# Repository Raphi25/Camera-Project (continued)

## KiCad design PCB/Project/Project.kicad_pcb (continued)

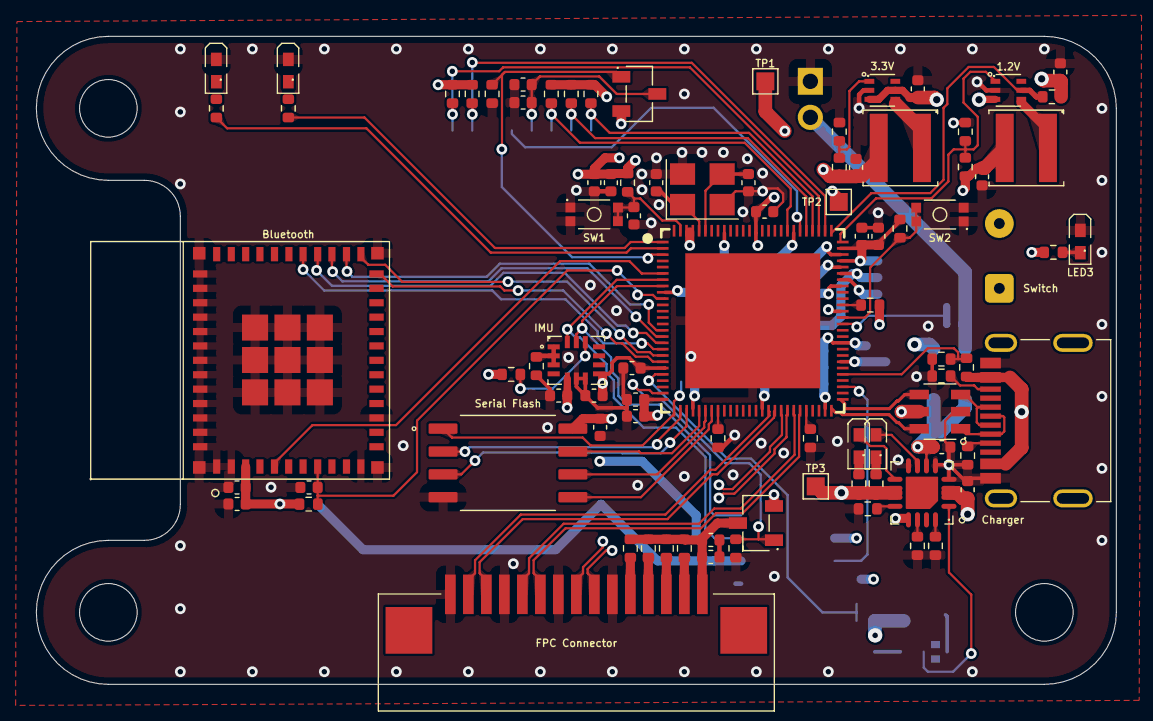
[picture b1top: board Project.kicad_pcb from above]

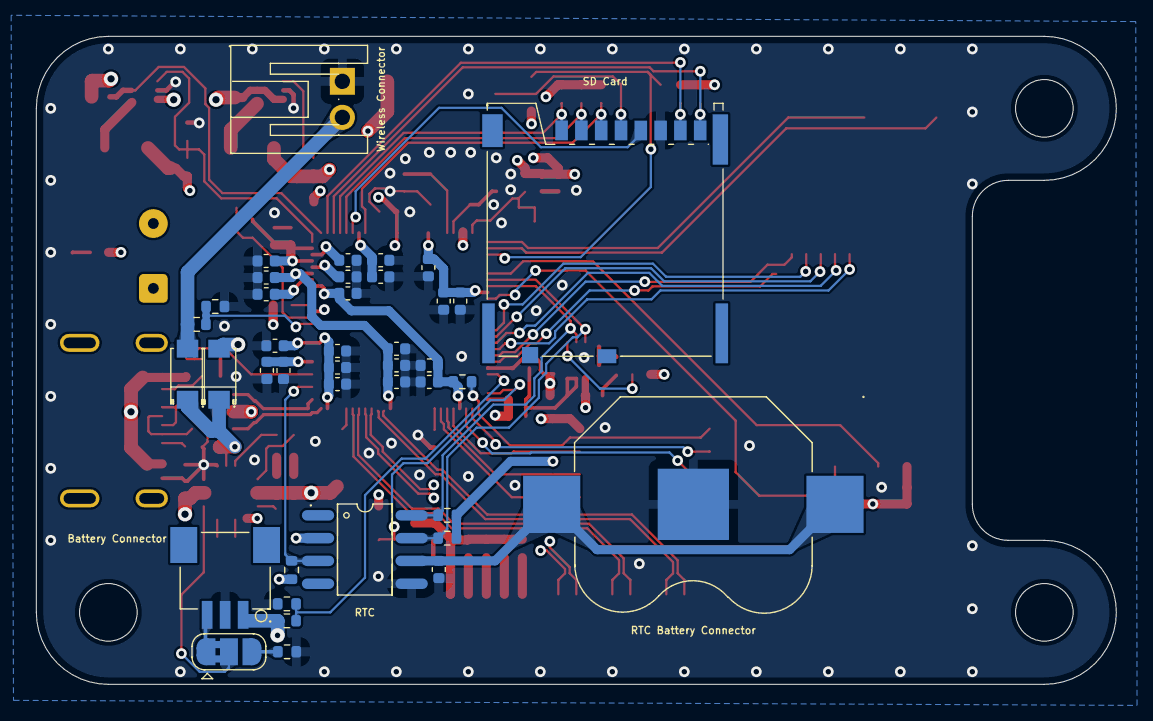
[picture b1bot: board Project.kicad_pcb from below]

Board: 4 copper layers, 60.0 x 36.0 mm, 132 parts (40 on the bottom side), 89 nets.

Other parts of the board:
1.2V, 3.3V: TLV62569PDRLR; SOT-563_L1.6-W1.2-P0.50-LS1.6-BL
Battery Connector: SM03B-SRSS-TB; CONN-SMD_SM03B-SRSS-TB-LF-SN-P
Bluetooth: ESP32-C6-MINI-1-N4; WIFIM-SMD_61P-L16.6-W13.2-P0.80-ESP32-C6-MINI-1-N4
Charger: BQ24074RGTR; QFN-16_L3.0-W3.0-P0.50-TL-EP1.7
FPC Connector: 1.0-15P下接; FPC-SMD_C66660
IMU: LSM6DSOTR; LGA-14_L3.0-W2.5-P0.50-TL
RTC: DS3231MZ+_C722467; SOIC-8_L4.9-W3.9-P1.27-LS6.0-BL
RTC Battery Connector: 3000; BAT-SMD_CR1202
SD Card: 503398-1892; TF-SMD_503398-1892
Serial Flash: W25Q128JVSIQ; SOIC127P790X216-8N
Switch: Conn_01x02; SolderWire-0.1sqmm_1x02_P3.6mm_D0.4mm_OD1mm
Wireless Connector: S2B-PH-K-S; CONN-TH_S2B-PH-K-S-LF-SN

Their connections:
+5V_CH: Charger.6 (EN1), Charger.13 (IN), RTC.2 (VCC); also elsewhere on the board
+5V_WIR: Wireless Connector.2; also elsewhere on the board
+BATT: Battery Connector.1, Charger.2 (BAT), Charger.3 (BAT); also elsewhere on the board
+BATT2: RTC.6 (VBAT), RTC Battery Connector.1 (+), RTC Battery Connector.2 (+); also elsewhere on the board
C6_EN: Bluetooth.8 (EN); also elsewhere on the board
C6_WAKEUP: Bluetooth.5 (IO2); also elsewhere on the board
CSI_CLK_N: FPC Connector.9; also elsewhere on the board
CSI_CLK_P: FPC Connector.8; also elsewhere on the board
CSI_D0_N: FPC Connector.2; also elsewhere on the board
CSI_D0_P: FPC Connector.3; also elsewhere on the board
CSI_D1_N: FPC Connector.5; also elsewhere on the board
CSI_D1_P: FPC Connector.6; also elsewhere on the board
EN_1.2V: 1.2V.5 (EN); also elsewhere on the board
ESP_3V3: Bluetooth.3 (3V3), IMU.5 (VDDIO), IMU.8 (VDD); also elsewhere on the board
ESP_LDO_VO1: Serial Flash.8 (VCC); also elsewhere on the board
ESP_SCL: IMU.13 (SCL), RTC.8 (SCL); also elsewhere on the board
ESP_SDA: IMU.14 (SDA), RTC.7 (SDA); also elsewhere on the board
FB_DCDC: 1.2V.1 (FB); also elsewhere on the board
FLASH_CK: Serial Flash.6 (CLK); also elsewhere on the board
FLASH_CS: Serial Flash.1 (/CS); also elsewhere on the board
FLASH_D: Serial Flash.5 (DI(IO0)); also elsewhere on the board
FLASH_HOLD: Serial Flash.7 (/HOLD/RESET(IO3)); also elsewhere on the board
FLASH_Q: Serial Flash.2 (DO(IO1)); also elsewhere on the board
FLASH_WP: Serial Flash.3 (/WP(IO2)); also elsewhere on the board
GND: 1.2V.2 (GND), 3.3V.2 (GND), Battery Connector.2, Bluetooth.1 (GND), Bluetooth.2 (GND), Bluetooth.11 (GND), Bluetooth.14 (GND), Bluetooth.36 (GND), Bluetooth.37 (GND), Bluetooth.38 (GND), Bluetooth.39 (GND), Bluetooth.40 (GND), Bluetooth.41 (GND), Bluetooth.42 (GND), Bluetooth.43 (GND), Bluetooth.44 (GND), Bluetooth.45 (GND), Bluetooth.46 (GND), Bluetooth.47 (GND), Bluetooth.48 (GND), Bluetooth.49 (GND), Bluetooth.50 (GND), Bluetooth.51 (GND), Bluetooth.52 (GND), Bluetooth.53 (GND), Charger.4 (~CE), Charger.5 (EN2), Charger.8 (VSS), FPC Connector.1, FPC Connector.4, FPC Connector.7, FPC Connector.10, IMU.6 (GND), IMU.7 (GND), RTC.5 (GND), RTC Battery Connector.3 (-), SD Card.6 (VSS), Serial Flash.4 (GND), Wireless Connector.1; also elsewhere on the board
unnamed 37: FPC Connector.11; also elsewhere on the board
unnamed 38: FPC Connector.12; also elsewhere on the board
unnamed 39: FPC Connector.13; also elsewhere on the board
unnamed 40: FPC Connector.14; also elsewhere on the board
unnamed 41: Charger.10 (OUT), Charger.11 (OUT), Switch.1; also elsewhere on the board
unnamed 42: Battery Connector.3; also elsewhere on the board
unnamed 45: Charger.9 (~CHG); also elsewhere on the board
unnamed 47: Charger.7 (~PGOOD); also elsewhere on the board
unnamed 51: FPC Connector.15; also elsewhere on the board
unnamed 52: SD Card.4 (VDD); also elsewhere on the board
unnamed 58: 3.3V.1 (FB); also elsewhere on the board
unnamed 59: 3.3V.4 (SW); also elsewhere on the board
unnamed 60: 1.2V.4 (SW); also elsewhere on the board
unnamed 61: Charger.12 (ILIM); also elsewhere on the board
unnamed 62: Charger.16 (ISET); also elsewhere on the board
unnamed 63: Charger.14 (TMR); also elsewhere on the board
unnamed 64: IMU.12 (CS); also elsewhere on the board
unnamed 65: IMU.1 (SDO/SA0), IMU.2 (SDX), IMU.3 (SCX); also elsewhere on the board
RTC_INT: RTC.3 (~INT/SQW); also elsewhere on the board
SD1_CLK: SD Card.5 (CLK); also elsewhere on the board
SD1_CMD: SD Card.3 (CMD); also elsewhere on the board
SD1_D0: SD Card.7 (DAT0); also elsewhere on the board
SD1_D1: SD Card.8 (DAT1); also elsewhere on the board
SD1_D2: SD Card.1 (DAT2); also elsewhere on the board
SD1_D3: SD Card.2 (CD/DAT3); also elsewhere on the board
SDIO_CLK: Bluetooth.25 (IO19); also elsewhere on the board
SDIO_CMD: Bluetooth.24 (IO18); also elsewhere on the board
SDIO_D0: Bluetooth.26 (IO20); also elsewhere on the board
SDIO_D1: Bluetooth.27 (IO21); also elsewhere on the board
SDIO_D2: Bluetooth.28 (IO22); also elsewhere on the board
SDIO_D3: Bluetooth.29 (IO23); also elsewhere on the board
TEMP: Charger.1 (TS); also elsewhere on the board
VBUS: 1.2V.3 (VIN), 3.3V.3 (VIN), 3.3V.5 (EN), Switch.2; also elsewhere on the board

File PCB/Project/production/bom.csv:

Designator,Footprint,Quantity,Value,LCSC Part #
BAT1,BAT-SMD_CR1202,1,3000,C238097
"C1, C38, C4, C40, C41, C42",0402,6,10uF,
"C10, C13, C15, C17, C18, C19, C20, C22, C26, C48, C49, C6",0402,12,1uF,
"C11, C36, C44, C8",0402,4,10nF,
"C12, C14, C16, C2, C21, C23, C24, C25, C27, C28, C3, C31, C32, C33, C34, C35, C43, C45, C46, C47, C5, C50, C7, C9",0402,24,100nF,
"C29, C30",0402,2,18pF,
"C37, C39",0402,2,4.7uF,
D1,SOT-23-6_L2.9-W1.6-P0.95-LS2.8-BL,1,USBLC6-2SC6,C7519
"D2, D3",SOD-123F_L2.7-W1.7-LS3.6-RD,2,PMEG2010ER-TP,C49231019
FPC1,FPC-SMD_C66660,1,1.0-15P下接,C66660
J1,SolderWire-0.1sqmm_1x02_P3.6mm_D0.4mm_OD1mm,1,Conn_01x02,
"LED1, LED2, LED3, LED4, LED5",LED0402-R-RD,5,16-213SURC/S530-A4/TR8,C74339
"Q1, Q2",SOT-23-3_L2.9-W1.3-P1.90-LS2.4-BR,2,AO3401A_C306862,C306862
"R1, R10, R13, R14, R16, R17, R18, R19, R20, R32, R34, R36, R4, R41, R42, R5, R9",0402,17,10kΩ,
R11,0402,1,5.1kΩ,
"R12, R15, R6",0402,3,51kΩ,
"R2, R3",0402,2,4.02kΩ,
R21,0402,1,450kΩ,
"R22, R23, R24, R25",0402,4,100kΩ,
R26,0402,1,1.6kΩ,
R27,0402,1,910Ω,
"R28, R29",0402,2,150Ω,
R30,0402,1,50kΩ,
R31,0402,1,750Ω,
R33,0402,1,24.9kΩ,
R35,0402,1,15kΩ,
R37,0402,1,330Ω,
"R38, R39, R7, R8",0402,4,2.2kΩ,
R40,0402,1,4.7kΩ,
"R43, R44, R45",0402,3,3.3kΩ,
SD1,TF-SMD_503398-1892,1,503398-1892,C428492
"SW1, SW2",SW-SMD_4P-L2.6-W1.6-P0.75-LS3.0,2,1TS026A-1000-0550-CT,C913778
"TP1, TP2, TP3",TestPoint_Pad_1.0x1.0mm,3,TestPoint,
U1,QFN-104_L10.0-W10.0-P0.35-TL-EP7.5,1,ESP32-P4NRW32X,C54540373
U10,WIFIM-SMD_61P-L16.6-W13.2-P0.80-ESP32-C6-MINI-1-N4,1,ESP32-C6-MINI-1-N4,C5736265
U11,LGA-14_L3.0-W2.5-P0.50-TL,1,LSM6DSOTR,C2655100
U12,SOIC-8_L4.9-W3.9-P1.27-LS6.0-BL,1,DS3231MZ+_C722467,C722467
U2,SOIC127P790X216-8N,1,W25Q128JVSIQ,
"U3, U4",SOT-563_L1.6-W1.2-P0.50-LS1.6-BL,2,TLV62569PDRLR,C398364
"U5, U6",IND-SMD_L4.0-W4.0-A,2,XAL4020-222MEC,C3151182
U7,QFN-16_L3.0-W3.0-P0.50-TL-EP1.7,1,BQ24074RGTR,C54313
U8,CONN-SMD_SM03B-SRSS-TB-LF-SN-P,1,SM03B-SRSS-TB,C160403
U9,CONN-TH_S2B-PH-K-S-LF-SN,1,S2B-PH-K-S,C173752
USB1,USB-C-SMD_2171790001,1,2171790001,C3197684
Y1,Crystal_SMD_3225-4Pin_3.2x2.5mm,1,Crystal_GND24_Small,
